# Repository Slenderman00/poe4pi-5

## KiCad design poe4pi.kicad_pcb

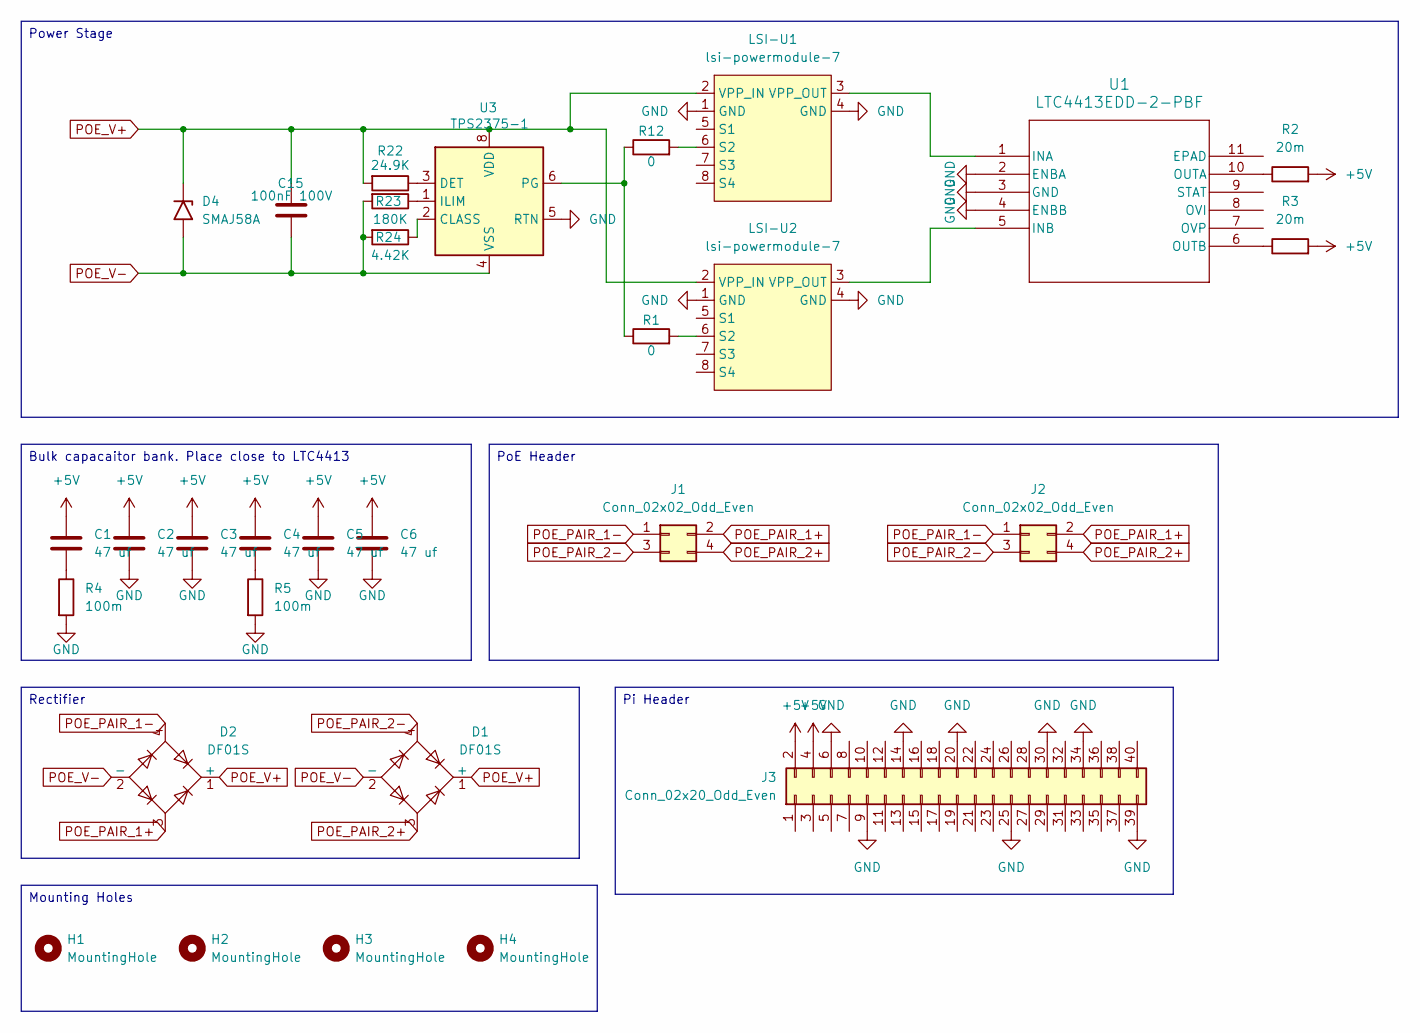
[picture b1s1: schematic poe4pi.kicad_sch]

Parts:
C1, C2, C3, C4, C5, C6: 47 uf; C_1210_3225Metric
C15: 100nF 100V; C_0402_1005Metric
D1, D2: DF01S; Diode_Bridge_OnSemi_SDIP-4L
D4: SMAJ58A; D_SMA
H1, H2, H3, H4: MountingHole; MountingHole_2.5mm
J1, J2: Conn_02x02_Odd_Even; PinSocket_2x02_P2.54mm_Vertical
J3: Conn_02x20_Odd_Even; PinHeader_2x20_P2.54mm_Vertical
LSI-U1, LSI-U2: lsi-powermodule-7
R1, R12: 0; R_0402_1005Metric
R2, R3: 20m; R_01005_0402Metric
R4, R5: 100m; R_1210_3225Metric
R22: 24.9K; R_0402_1005Metric
R23: 180K; R_0402_1005Metric
R24: 4.42K; R_0402_1005Metric
U1: LTC4413EDD-2-PBF; DFN-10_DD_LIT
U3: TPS2375-1; TSSOP-8_4.4x3mm_P0.65mm

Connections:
+5V: C1.1, C2.1, C3.1, C4.1, C5.1, C6.1, J3.2, J3.4, R2.2, R3.2
GND: C2.2, C3.2, C5.2, C6.2, J3.6, J3.9, J3.14, J3.20, J3.25, J3.30, J3.34, J3.39, LSI-U1.1 (GND), LSI-U1.4 (GND), LSI-U2.1 (GND), LSI-U2.4 (GND), R4.2, R5.2, U1.2 (ENBA), U1.3 (GND), U1.4 (ENBB), U3.5 (RTN)
unnamed: C1.2, R4.1
unnamed: C4.2, R5.1
unnamed: LSI-U1.6 (S2), R12.2
unnamed: LSI-U1.3 (VPP_OUT), U1.1 (INA)
unnamed: LSI-U2.6 (S2), R1.2
unnamed: LSI-U2.3 (VPP_OUT), U1.5 (INB)
unnamed: R2.1, U1.10 (OUTA)
unnamed: R3.1, U1.6 (OUTB)
unnamed: R24.1, U3.2 (CLASS)
unnamed: R22.1, U3.3 (DET)
unnamed: R23.1, U3.1 (ILIM)
unnamed: R1.1, R12.1, U3.6 (PG)
POE_PAIR_1+: D2.3, J1.2, J2.2
POE_PAIR_1-: D2.4, J1.1, J2.1
POE_PAIR_2+: D1.3, J1.4, J2.4
POE_PAIR_2-: D1.4, J1.3, J2.3
POE_V+: C15.1, D1.1 (+), D2.1 (+), D4.1 (A1), LSI-U1.2 (VPP_IN), LSI-U2.2 (VPP_IN), R22.2, U3.8 (VDD)
POE_V-: C15.2, D1.2 (-), D2.2 (-), D4.2 (A2), R23.2, R24.2, U3.4 (VSS)

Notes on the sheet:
Power Stage
PoE Header
Pi Header
Rectifier
Mounting Holes
Bulk capacaitor bank. Place close to LTC4413

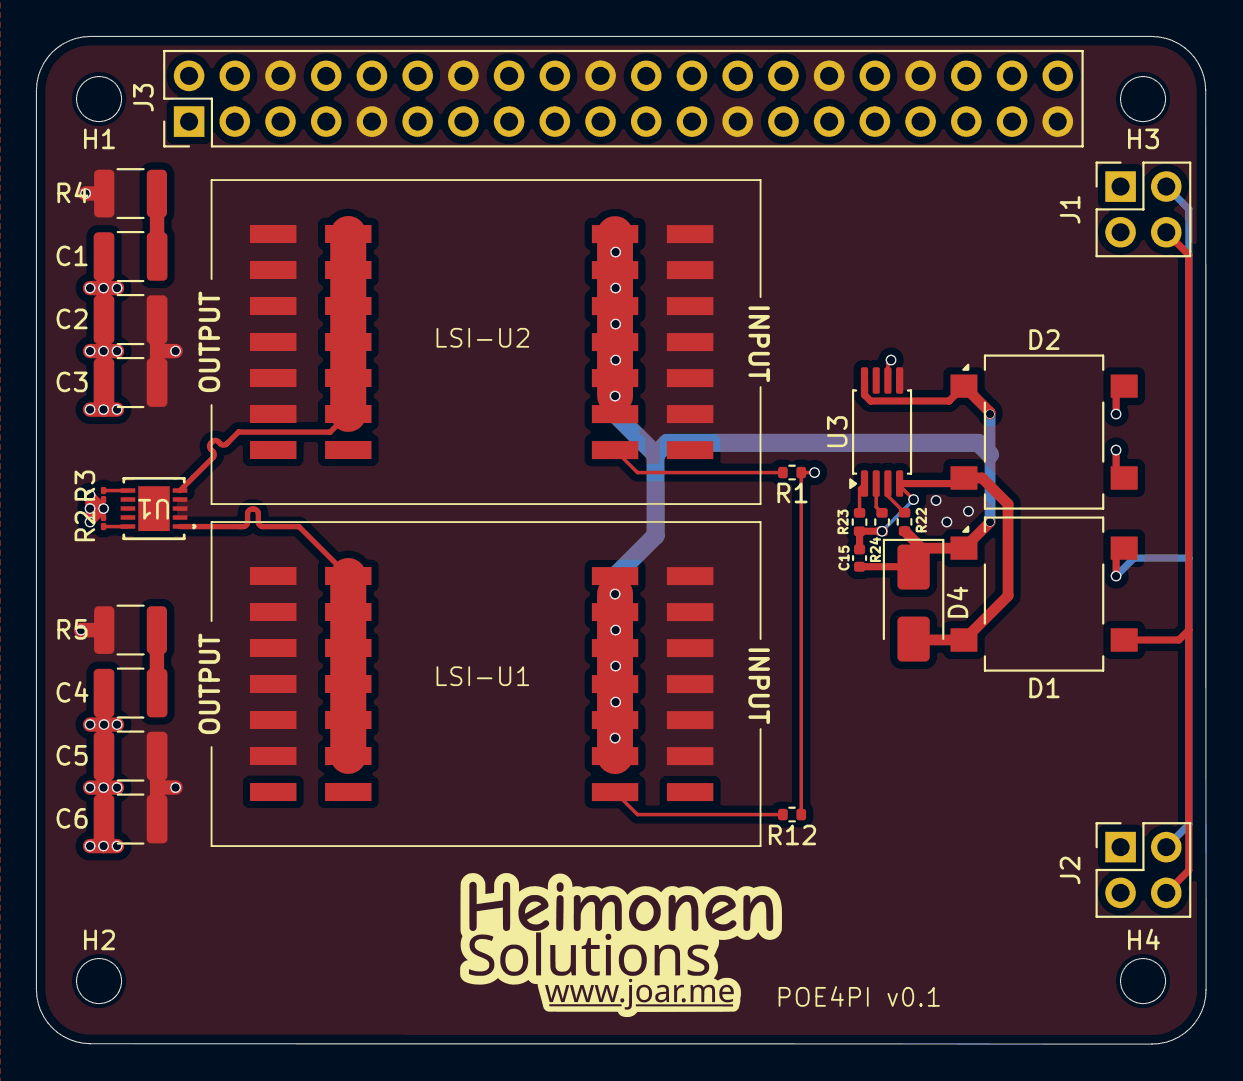
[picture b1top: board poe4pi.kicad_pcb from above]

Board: 4 copper layers, 65.0 x 56.0 mm, 30 parts (0 on the bottom side), 20 nets.

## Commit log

2025-10-23 feat: initial version
2025-10-23 feat: schematic
2025-10-24 feat: header placement
2025-10-24 feat: initial layout
2025-10-24 feat: v0.1
2025-10-24 feat: production files
2025-10-25 fix: vias
